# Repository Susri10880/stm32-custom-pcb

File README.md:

# STM32 Custom PCB Design (Practice Project)

This repository contains a **practice schematic** for an STM32-based custom PCB design created using **KiCad EDA**.  
It is **not a manufactured board** — intended purely for learning and experimentation with schematic design and layout principles.

---

## 🧩 Overview

The design features an **STM32F103C8T6** microcontroller and includes:
- **Power Regulation**: AMS1117-3.3 voltage regulator circuit for USB 5V to 3.3V conversion.
- **Microcontroller Core**: STM32F103C8T6 with crystal oscillator (16 MHz), reset and boot circuitry.
- **USB Interface**: Micro‑USB connector for power and communication.
- **Peripheral Headers**: USART, I²C, and GPIO pin headers for external interfacing.
- **Mounting Holes**: For mechanical support and PCB placement.

---

## ⚙️ Tools Used
- **KiCad Version**: 10.0.3  
- **File Types**:
  - `.kicad_pro` – Project file  
  - `.kicad_sch` – Schematic file  
  - `.kicad_pcb` – PCB layout (if applicable)  
  - Custom symbol and footprint libraries (if used)

---

## 🧠 Purpose
This project serves as a **learning exercise** to:
- Practice schematic capture and PCB layout in KiCad.
- Understand STM32 microcontroller pinouts and peripheral connections.
- Explore power regulation and USB interface design.

---

## ⚠️ Disclaimer
> This schematic is **for educational and testing purposes only**.  
> It has **not been fabricated or electrically tested**.  
> Do not use it for production or safety‑critical applications.

---

## 📸 Preview

---

## 🧾 License
You may freely use, modify, and share this design for **non‑commercial educational purposes**.

---

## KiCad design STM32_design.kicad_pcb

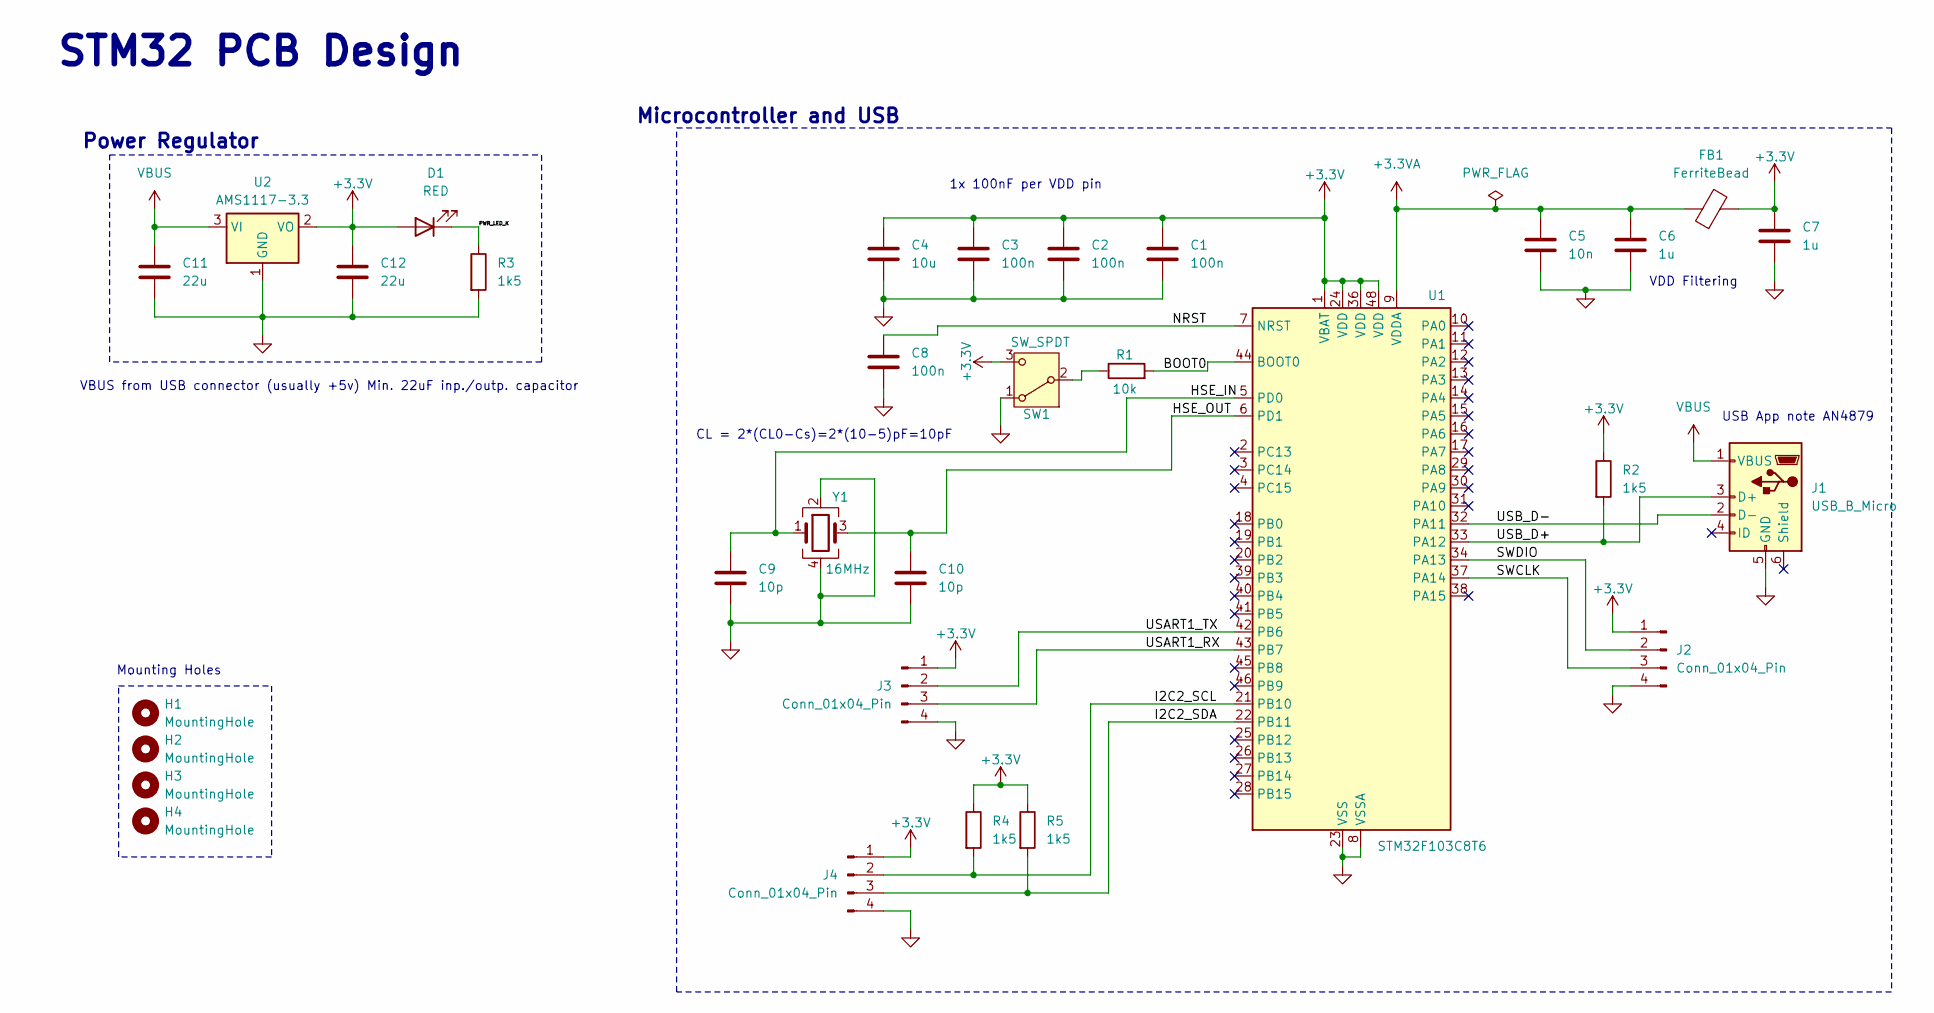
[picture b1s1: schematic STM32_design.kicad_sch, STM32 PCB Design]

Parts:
C1, C2, C3, C8: 100n; C_0402_1005Metric
C4: 10u; C_0603_1608Metric
C5: 10n; C_0402_1005Metric
C6, C7: 1u; C_0402_1005Metric
C9, C10: 10p; C_0402_1005Metric
C11, C12: 22u; C_0805_2012Metric
D1: RED; LED_0603_1608Metric
FB1: FerriteBead; L_0603_1608Metric
H1, H2, H3, H4: MountingHole; MountingHole_2.2mm_M2
J1: USB_B_Micro; USB_Micro-B_Wuerth_629105150521
J2, J3, J4: Conn_01x04_Pin; PinHeader_1x04_P2.54mm_Vertical
R1: 10k; R_0402_1005Metric
R2, R3, R4, R5: 1k5; R_0402_1005Metric
SW1: SW_SPDT; SW_SPDT_PCM12
U1: STM32F103C8T6; LQFP-48_7x7mm_P0.5mm
U2: AMS1117-3.3; SOT-223-3_TabPin2
Y1: 16MHz; Crystal_SMD_3225-4Pin_3.2x2.5mm

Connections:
+3.3V: C1.1, C2.1, C3.1, C4.1, C7.1, C12.1, D1.2 (A), FB1.2, J2.1, J3.1, J4.1, R2.1, R4.1, R5.1, SW1.3 (C), U1.1 (VBAT), U1.24 (VDD), U1.36 (VDD), U1.48 (VDD), U2.2 (VO)
+3.3VA: C5.1, C6.1, FB1.1, U1.9 (VDDA)
/BOOT0: R1.2, U1.44 (BOOT0)
/HSE_IN: C9.1, U1.5 (PD0), Y1.1
/HSE_OUT: C10.1, U1.6 (PD1), Y1.3
/I2C2_SCL: J4.2, R4.2, U1.21 (PB10)
/I2C2_SDA: J4.3, R5.2, U1.22 (PB11)
/NRST: C8.1, U1.7 (NRST)
/PWR_LED_K: D1.1 (K), R3.1
/SWCLK: J2.3, U1.37 (PA14)
/SWDIO: J2.2, U1.34 (PA13)
/USART1_RX: J3.3, U1.43 (PB7)
/USART1_TX: J3.2, U1.42 (PB6)
/USB_D+: J1.3 (D+), R2.2, U1.33 (PA12)
/USB_D-: J1.2 (D-), U1.32 (PA11)
GND: C1.2, C2.2, C3.2, C4.2, C5.2, C6.2, C7.2, C8.2, C9.2, C10.2, C11.2, C12.2, J1.5 (GND), J2.4, J3.4, J4.4, R3.2, SW1.1 (A), U1.8 (VSSA), U1.23 (VSS), U1.35 (VSS), U1.47 (VSS), U2.1 (GND), Y1.2, Y1.4
unnamed: R1.1, SW1.2 (B)
VBUS: C11.1, J1.1 (VBUS), U2.3 (VI)

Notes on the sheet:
CL = 2*(CL0-Cs)=2*(10-5)pF=10pF
USB App note AN4879
VBUS from USB connector (usually +5v) Min. 22uF inp./outp. capacitor
Microcontroller and USB
STM32 PCB Design
Power Regulator
1x 100nF per VDD pin
Mounting Holes
VDD Filtering

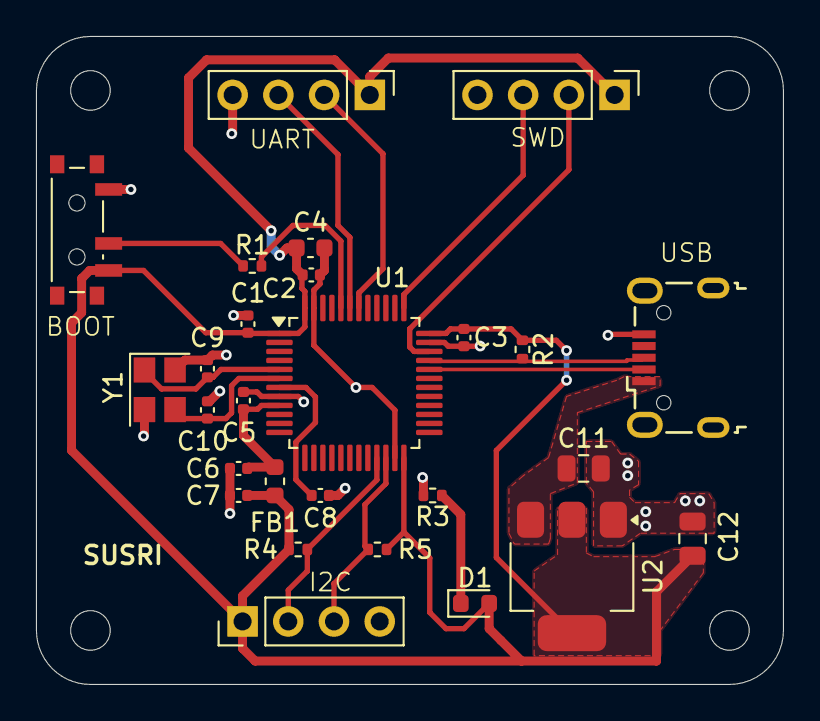
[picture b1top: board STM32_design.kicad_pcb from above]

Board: 2 copper layers, 41.5 x 36.0 mm, 31 parts (0 on the bottom side), 18 nets.
